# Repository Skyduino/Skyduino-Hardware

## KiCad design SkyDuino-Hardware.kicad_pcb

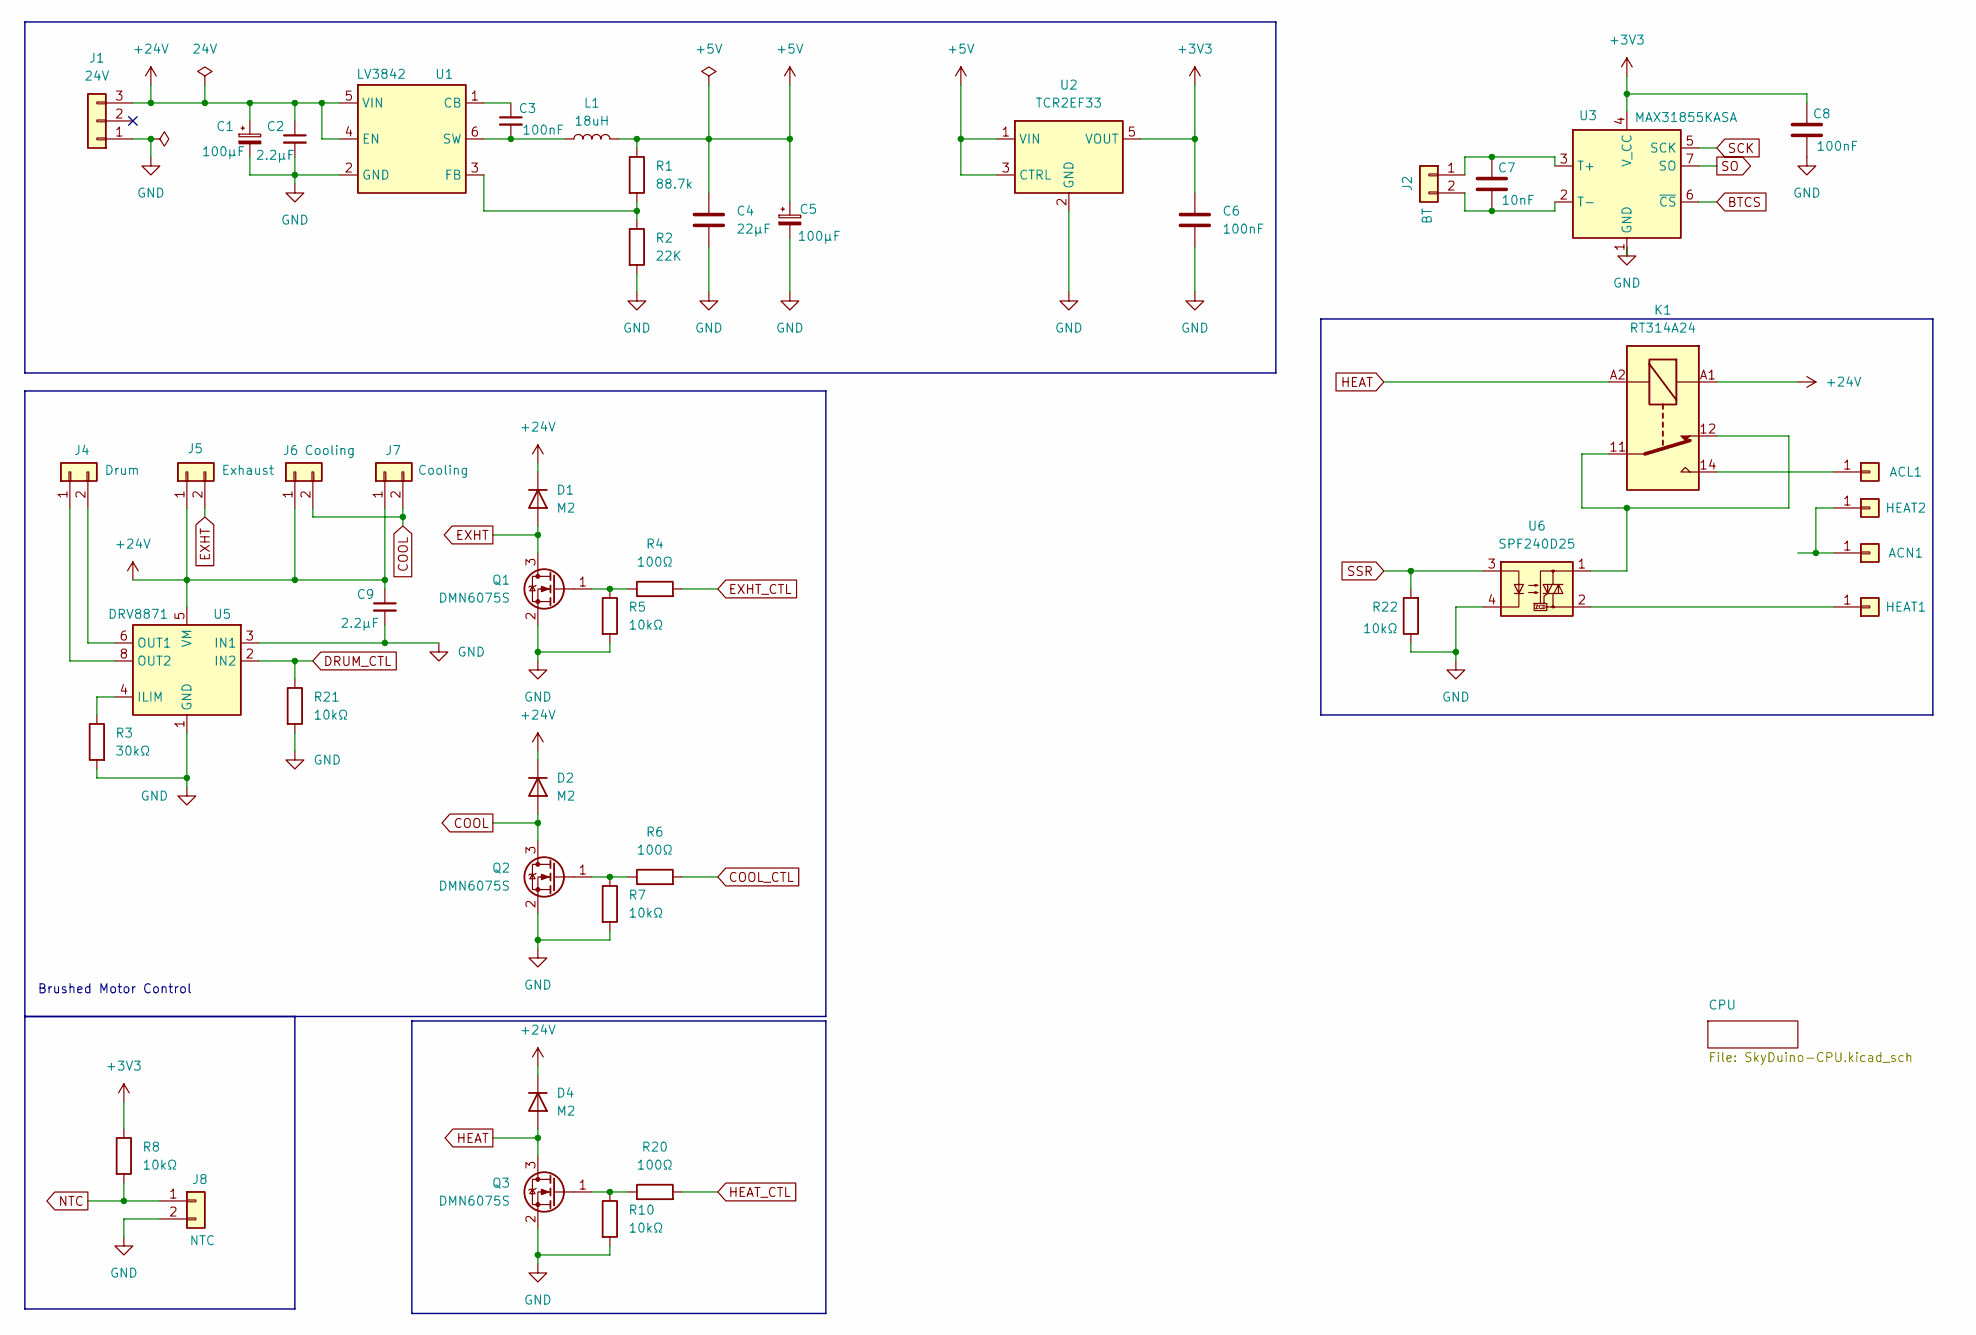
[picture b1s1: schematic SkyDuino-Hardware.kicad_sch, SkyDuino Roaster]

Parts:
ACL1: QC 19705-4303; QuickConnect_Tab_Molex_19705-4303; Mouser p/n 538-19705-4303
ACN1: QC 19705-4303; QuickConnect_Tab_Molex_19705-4303; Mouser p/n 538-19705-4303
C1, C5: 100µF; CP_Radial_D10.0mm_P5.00mm; Mouser p/n 667-ECA-2AM101
C2, C9: 2.2µF; C_0805_2012Metric_Pad1.18x1.45mm_HandSolder; Mouser p/n 187-CL21B225KPFNNNF; LCSC C377773
C3, C6, C8: 100nF; C_0805_2012Metric_Pad1.18x1.45mm_HandSolder; Mouser p/n 810-C2012X7R2A104K; LCSC C49678
C4: 22µF; C_0805_2012Metric_Pad1.18x1.45mm_HandSolder; Mouser p/n 810-C2012X5R1V226MAC; LCSC C45783
C7: 10nF; C_0805_2012Metric_Pad1.18x1.45mm_HandSolder; Mouser p/n 810-C2012C0G1H103J-1; LCSC C1710
D1, D2, D4: M2; D_SMA_Handsoldering; Mouser p/n 637-M2; LCSC C14996
HEAT1, HEAT2: QC 19705-4303; QuickConnect_Tab_Molex_19705-4303; Mouser p/n 538-19705-4303
J1: 24V; JST_XH_B3B-XH-A_1x03_P2.50mm_Vertical
J2: BT; KF7.62_2P
J4: Drum; JST_XH_B2B-XH-A_1x02_P2.50mm_Vertical
J5: Exhaust; JST_XH_B2B-XH-A_1x02_P2.50mm_Vertical
J6, J7: Cooling; JST_XH_B2B-XH-A_1x02_P2.50mm_Vertical
J8: NTC; JST_XH_B2B-XH-A_1x02_P2.50mm_Vertical
K1: RT314A24; Relay_SPDT_Schrack-RT1-16A-FormC_RM5mm; Mouser p/n 655-RT314024
L1: 18uH; L_Bourns_SRN3015BTA; Mouser p/n 652-SRN3015BTA-180M; LCSC C19947604
Q1, Q2, Q3: DMN6075S; SOT-23; Mouser p/n 621-DMN6075S-7; LCSC C155242
R1: 88.7k; R_0805_2012Metric_Pad1.20x1.40mm_HandSolder; Mouser p/n 667-ERA-6AEB8872V; LCSC C706252
R2: 22K; R_0805_2012Metric_Pad1.20x1.40mm_HandSolder; Mouser p/n 603-RT0805DRE0722KL; LCSC C17560
R3: 30kΩ; R_0805_2012Metric_Pad1.20x1.40mm_HandSolder; Mouser p/n 603-RC0805FR-0730KL; LCSC C17633
R4, R6, R20: 100Ω; R_0805_2012Metric_Pad1.20x1.40mm_HandSolder; Mouser p/n 603-AC0805FR-10100RL; LCSC C17408
R5, R7, R8, R10, R21, R22: 10kΩ; R_0805_2012Metric_Pad1.20x1.40mm_HandSolder; Mouser p/n 603-AC0805JR-0710KL; LCSC C17414
U1: LV3842; SOT-23-6; Mouser p/n 595-LV3842XFDBVR; LCSC C5219371
U2: TCR2EF33; SC-74A-5_1.55x2.9mm_P0.95mm; Mouser p/n 757-TCR2EF33LMCT; LCSC C843273
U3: MAX31855KASA; SOIC-8_3.9x4.9mm_P1.27mm; Mouser p/n 700-MAX31855KASA+T; LCSC C52028
U5: DRV8871; Texas_HTSOP-8-1EP_3.9x4.9mm_P1.27mm_EP2.95x4.9mm_Mask2.4x3.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; Mouser p/n 595-DRV8871DDA; LCSC C75864
U6: SPF240D25; SSR_Crydom_SPF240D25; Mouser p/n 558-SPF240D25

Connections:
+3V3: C6.1, C8.1, R8.1, U2.5 (VOUT), U3.4 (V_CC); also elsewhere on the board
+5V: C4.1, C5.1, L1.2, R1.1, U2.1 (VIN), U2.3 (CTRL); also elsewhere on the board
+24V: C1.1, C2.1, C9.1, D1.1 (K), D2.1 (K), D4.1 (K), J1.3, J5.1, J6.1, J7.1, K1.A1, U1.4 (EN), U1.5 (VIN), U5.5 (VM)
BTCS: U3.6 (~CS); also elsewhere on the board
COOL: D2.2 (A), J6.2, J7.2, Q2.3 (D)
COOL_CTL: R6.2; also elsewhere on the board
DRUM_CTL: R21.1, U5.2 (IN2); also elsewhere on the board
EXHT: D1.2 (A), J5.2, Q1.3 (D)
EXHT_CTL: R4.2; also elsewhere on the board
GND: C1.2, C2.2, C4.2, C5.2, C6.2, C8.2, C9.2, J1.1, J8.2, Q1.2 (S), Q2.2 (S), Q3.2 (S), R2.2, R3.2, R5.2, R7.2, R10.2, R21.2, R22.1, U1.2 (GND), U2.2 (GND), U3.1 (GND), U5.1 (GND), U5.3 (IN1), U5.7 (GND), U5.9 (GND), U6.4; also elsewhere on the board
HEAT: D4.2 (A), K1.A2, Q3.3 (D)
HEAT_CTL: R20.2; also elsewhere on the board
NTC: J8.1, R8.2; also elsewhere on the board
unnamed: ACL1.1, K1.14
unnamed: ACN1.1, HEAT2.1
unnamed: HEAT1.1, U6.2
unnamed: C7.1, J2.1, U3.3 (T+)
unnamed: C7.2, J2.2, U3.2 (T-)
unnamed: J4.1, U5.8 (OUT2)
unnamed: J4.2, U5.6 (OUT1)
unnamed: K1.11, K1.12, U6.1
unnamed: Q1.1 (G), R4.1, R5.1
unnamed: Q2.1 (G), R6.1, R7.1
unnamed: Q3.1 (G), R10.1, R20.1
unnamed: C3.1, U1.1 (CB)
unnamed: R1.2, R2.1, U1.3 (FB)
unnamed: C3.2, L1.1, U1.6 (SW)
unnamed: R3.1, U5.4 (ILIM)
SCK: U3.5 (SCK); also elsewhere on the board
SO: U3.7 (SO); also elsewhere on the board
SSR: R22.2, U6.3; also elsewhere on the board

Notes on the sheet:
Brushed Motor Control

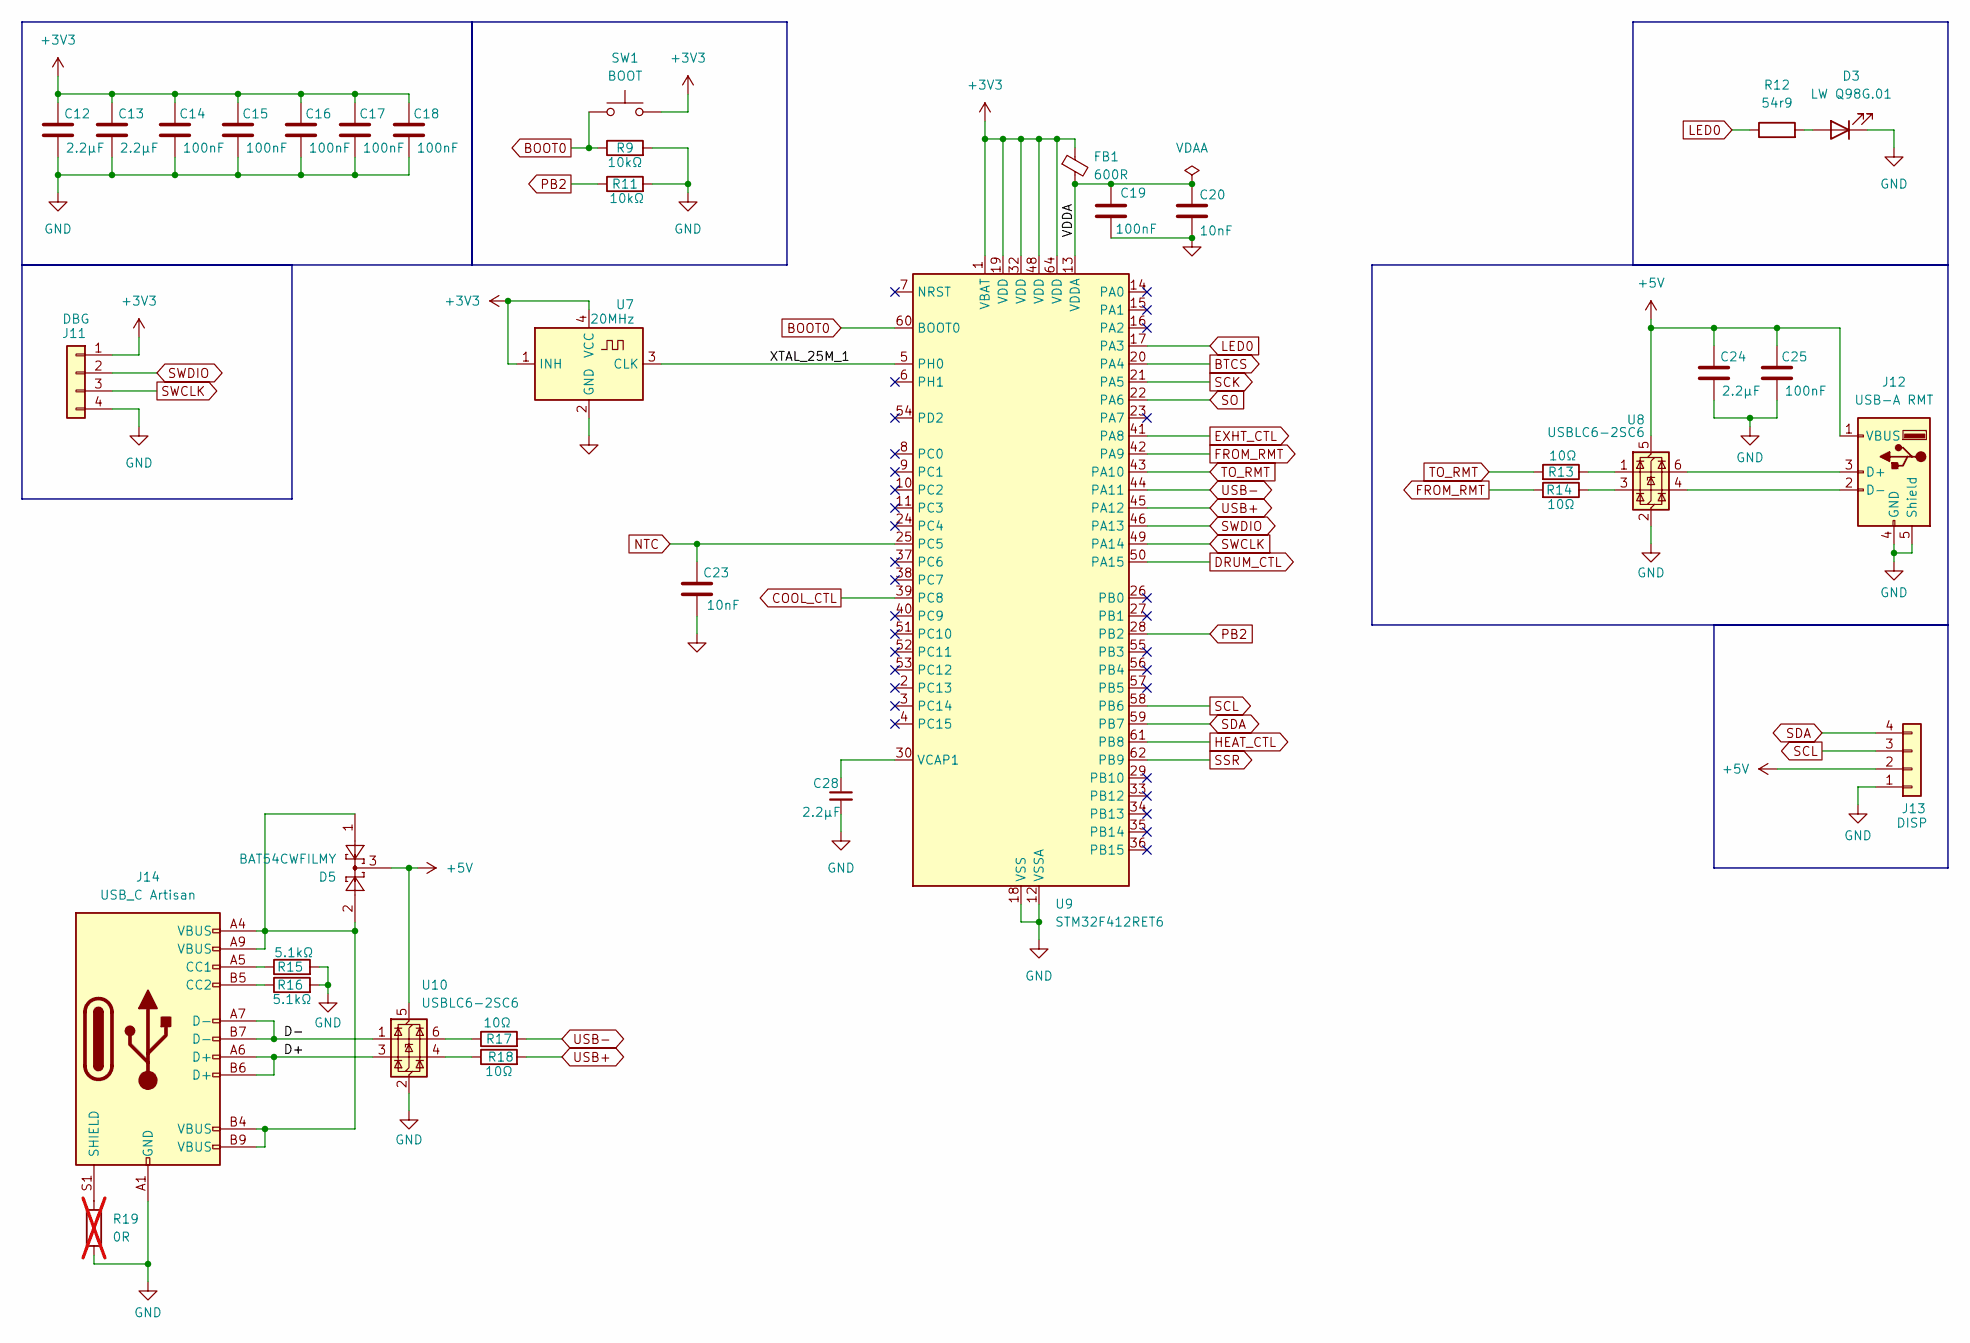
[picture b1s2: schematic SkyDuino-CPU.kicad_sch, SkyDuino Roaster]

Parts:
C12, C13, C24, C28: 2.2µF; C_0805_2012Metric_Pad1.18x1.45mm_HandSolder; Mouser p/n 187-CL21B225KPFNNNF; LCSC C377773
C14, C15, C16, C17, C18, C19, C25: 100nF; C_0805_2012Metric_Pad1.18x1.45mm_HandSolder; Mouser p/n 810-C2012X7R2A104K; LCSC C49678
C20, C23: 10nF; C_0805_2012Metric_Pad1.18x1.45mm_HandSolder; Mouser p/n 810-C2012C0G1H103J-1; LCSC C1710
D3: LW Q98G.01; LED_0805_2012Metric_Pad1.15x1.40mm_HandSolder; Mouser p/n 720-LWQ98G01R2T13K6L; LCSC C34499
D5: BAT54CWFILMY; SOT-323_SC-70; Mouser p/n 511-BAT54CWFILMY; LCSC C2980568
FB1: 600R; L_0805_2012Metric_Pad1.05x1.20mm_HandSolder; Mouser p/n 810-MMZ2012R601AT000; LCSC C1017
J11: DBG; PinHeader_1x04_P2.54mm_Vertical
J12: USB-A RMT; USB_A_Molex_67643_Horizontal_and_AmphenolFCI_87583; Mouser p/n 538-67643-0910
J13: DISP; PinHeader_1x04_P2.54mm_Vertical
J14: USB_C Artisan; USB_C_Receptacle_Molex_Upright; Mouser p/n 538-216989-0001
R9, R11: 10kΩ; R_0805_2012Metric_Pad1.20x1.40mm_HandSolder; Mouser p/n 603-AC0805JR-0710KL; LCSC C17414
R12: 54r9; R_0805_2012Metric_Pad1.20x1.40mm_HandSolder; Mouser p/n 667-ERJ-6ENF54R9V; LCSC C17408
R13, R14, R17, R18: 10Ω; R_0805_2012Metric_Pad1.20x1.40mm_HandSolder; Mouser p/n 603-RC0805FR-1010RL; LCSC C17415
R15, R16: 5.1kΩ; R_0805_2012Metric_Pad1.20x1.40mm_HandSolder; Mouser p/n 603-RC0805JR-135K1L; LCSC C27834
R19: 0R; R_0805_2012Metric_Pad1.20x1.40mm_HandSolder; not fitted
SW1: BOOT; SW_PUSH_6mm_H4.3mm
U7: 20MHz; Oscillator_SMD_Kyocera_KC2520Z-4Pin_2.5x2.0mm; Manufacturer p/n SX2M20.000B10F20TNN; LCSC C7431315
U8, U10: USBLC6-2SC6; SOT-23-6; Mouser p/n 511-USBLC6-2SC6; LCSC C7519
U9: STM32F412RET6; LQFP-64_10x10mm_P0.5mm; Mouser p/n 511-STM32F412RET6; LCSC STM32F412RET6

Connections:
+3V3: C12.1, C13.1, C14.1, C15.1, C16.1, C17.1, C18.1, FB1.1, J11.1, SW1.2, U7.1 (INH), U7.4 (VCC), U9.1 (VBAT), U9.19 (VDD), U9.32 (VDD), U9.48 (VDD), U9.64 (VDD); also elsewhere on the board
+5V: C24.1, C25.1, D5.3, J12.1 (VBUS), J13.2, U8.5 (VBUS), U10.5 (VBUS); also elsewhere on the board
/CPU/D+: J14.A6 (D+), J14.B6 (D+), U10.3 (I/O2)
/CPU/D-: J14.A7 (D-), J14.B7 (D-), U10.1 (I/O1)
/CPU/VDDA: C19.2, C20.2, FB1.2, U9.13 (VDDA)
/CPU/XTAL_25M_1: U7.3 (CLK), U9.5 (PH0)
BOOT0: R9.1, SW1.1, U9.60 (BOOT0)
BTCS: U9.20 (PA4); also elsewhere on the board
COOL_CTL: U9.39 (PC8); also elsewhere on the board
DRUM_CTL: U9.50 (PA15); also elsewhere on the board
EXHT_CTL: U9.41 (PA8); also elsewhere on the board
FROM_RMT: R14.2, U9.42 (PA9)
GND: C12.2, C13.2, C14.2, C15.2, C16.2, C17.2, C18.2, C19.1, C20.1, C23.2, C24.2, C25.2, C28.2, D3.1 (K), J11.4, J12.4 (GND), J12.5 (Shield), J13.1, J14.A1 (GND), J14.A12 (GND), J14.B1 (GND), J14.B12 (GND), R9.2, R11.2, R15.2, R16.2, R19.2, U7.2 (GND), U8.2 (GND), U9.12 (VSSA), U9.18 (VSS), U9.31 (VSS), U9.47 (VSS), U9.63 (VSS), U10.2 (GND); also elsewhere on the board
HEAT_CTL: U9.61 (PB8); also elsewhere on the board
LED0: R12.1, U9.17 (PA3)
NTC: C23.1, U9.25 (PC5); also elsewhere on the board
unnamed: D3.2 (A), R12.2
unnamed: D5.1, D5.2, J14.A4 (VBUS), J14.A9 (VBUS), J14.B4 (VBUS), J14.B9 (VBUS)
unnamed: J12.3 (D+), U8.6 (I/O1)
unnamed: J12.2 (D-), U8.4 (I/O2)
unnamed: J14.A5 (CC1), R15.1
unnamed: J14.B5 (CC2), R16.1
unnamed: J14.S1 (SHIELD), R19.1
unnamed: R13.1, U8.1 (I/O1)
unnamed: R14.1, U8.3 (I/O2)
unnamed: R17.1, U10.6 (I/O1)
unnamed: R18.1, U10.4 (I/O2)
unnamed: C28.1, U9.30 (VCAP1)
PB2: R11.1, U9.28 (PB2)
SCK: U9.21 (PA5); also elsewhere on the board
SCL: J13.3, U9.58 (PB6)
SDA: J13.4, U9.59 (PB7)
SO: U9.22 (PA6); also elsewhere on the board
SSR: U9.62 (PB9); also elsewhere on the board
SWCLK: J11.3, U9.49 (PA14)
SWDIO: J11.2, U9.46 (PA13)
TO_RMT: R13.2, U9.43 (PA10)
USB+: R18.2, U9.45 (PA12)
USB-: R17.2, U9.44 (PA11)

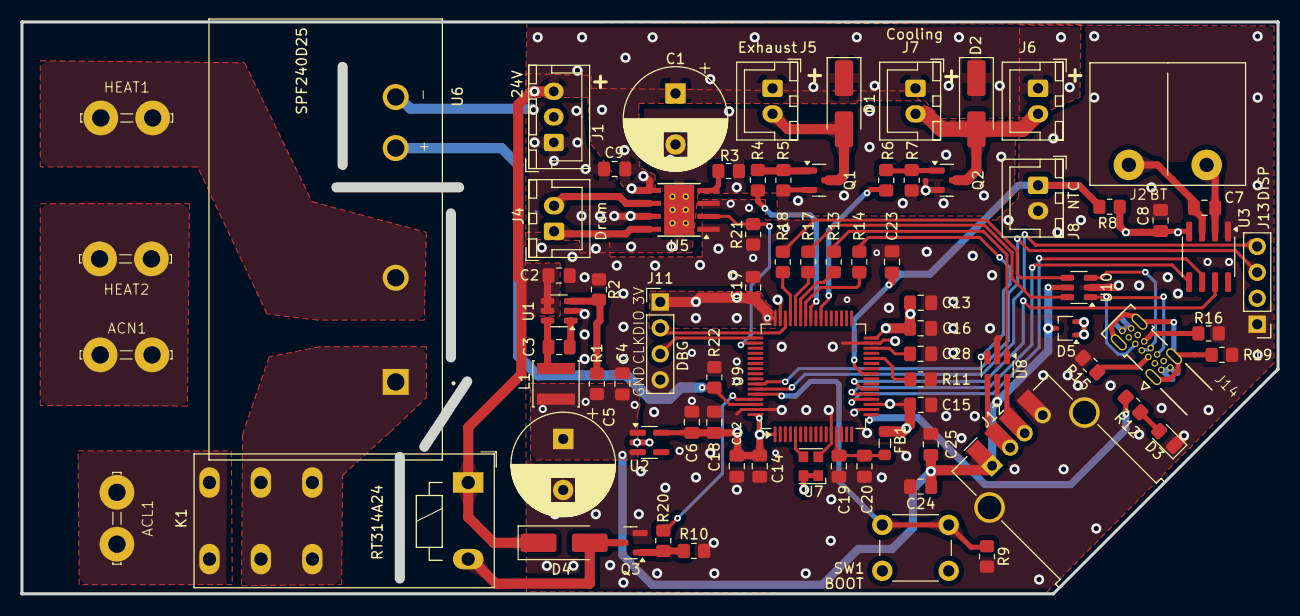
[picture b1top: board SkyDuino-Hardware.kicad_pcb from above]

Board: 4 copper layers, 122.3 x 55.3 mm, 80 parts (0 on the bottom side), 58 nets.

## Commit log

2024-05-04 Add LDO and Motor Controls
    - Add 3v3 LDO
    - Add Motor controls
2024-05-04 Add Max33851 for BT
2024-05-04 Add KF 7.62mm footprint
2024-05-04 Move project footprints libraries into its own folder
2024-05-04 Add Exhaust Temp probe
2024-05-04 Add CPU sheet
2024-05-04 WIP CPU
2024-05-04 WIP CPU boot switches
2024-05-04 Update gitignore
2024-05-04 Add Oscillators
2024-05-04 Rough in on MCU control connections
2024-05-04 Add USB-C connector
2024-05-04 Rename Connector_SH FPs lib
2024-05-04 Update KF7.64 footprint
2024-05-04 Add Footprint for USB-C receptacle
2024-05-05 Update footprint for the boot button
2024-05-06 Add USB-A for the remote
2024-05-07 Add VBat to VDD
2024-05-07 Add two extra 24v connectors
2024-05-07 Add NTC connection
2024-05-07 Add I2C for the display
2024-05-07 Re-annotate. Add NTC capacitor
2024-05-07 Add SSR
2024-05-08 Add Quick Connect Tabs and footprints
2024-05-09 Update footprints
2024-05-09 Use ferrite bead for AVDD
2024-05-09 Optimize pinouts
2024-05-09 Update PCB constraints
2024-05-09 Remove ET TC
2024-05-09 Optimize pinouts, update 2.2uF caps
2024-05-09 PCB WIP
2024-05-10 Mark unconnected STM32 pins
2024-05-11 Add Net Classes
2024-05-11 Add 3d Models
2024-05-11 Rearrange components. Fix 25MHz oscillator connection
2024-05-12 Update USB-C footprint
2024-05-12 WIP PCB tracing
2024-05-12 Remove 25MHz load cap
2024-05-12 Optimize SSR pin
2024-05-12 Optimize LED pin
2024-05-12 PCB Signalling routing
2024-05-12 Copper fill for power
2024-05-12 Label AC lines
2024-05-12 Pour AC lines
2024-05-12 Fix DRC vialations
2024-05-13 Unhide USB-C rec VBUS pins
2024-05-13 Update USB-A 3d model
2024-05-13 update footprint for resistors to hand solder
2024-05-13 Update sheet settings. Add revision text to pcb
2024-05-13 Update 5v pour
2024-05-13 Use same 100nF cap everywhere
2024-05-14 Bump up revision 0.2
2024-05-14 Refactor power rail and optimize pours
2024-05-14 Move SSR GND connection to B layer
2024-05-14 Add silkscreen for DBG/DISP
2024-05-16 Add Heat Safety relay
2024-05-16 WIP DRC
2024-05-17 Use VBus for 3V3 LDO
2024-05-17 Should have saved before commiting
2024-05-22 It is supposed to be STM32F41*2*RET6 MCU
2024-05-29 Move values to User.1 layer
2024-05-29 Refactor VBus/5v feeding
2024-05-30 Update PCB with VBus/5v changes
2024-05-30 Add pull down resistors for SSR and Drum control
2024-05-30 Bump up revision. Use text variables for version control
2024-05-31 Add License
2024-05-31 Fix cutouts, make those 1mm width
2024-05-31 Update symbol fields
2024-05-31 Add kibot file
2024-06-01 Fix KF7.62 FP DRC warnings
2024-06-01 Fix LV3842 ERC warnings
2024-06-01 Fix ERC/DRC warnings
2024-06-01 Update kibot config
2024-06-01 Fix warning for the step down converter
2024-06-01 Ibom extra fields and printing fixes
2024-06-01 Add User.1 layer to PDF fab layers printout
2024-06-01 cleanups
2024-06-01 Exclude project bak files from version control
2024-06-01 Filter DRC edge errors caused by cutouts
2024-06-01 Mostly copper pours optimizations
2024-06-01 Update Kibot PDF output, include inner copper layers
2024-06-01 fixup
2024-06-01 No blender rendering, because of the edge cutouts
2024-06-01 Initial Github Action
2024-06-02 Alow manual action call
2024-06-03 GHA: Duh
2024-06-03 Don't silk variant on PCB
2024-06-03 GHA: fixup
2024-06-03 Always upload artifacts
2024-06-03 GHA: can't spell...
2024-06-03 Rename GHA action
2024-06-03 Fix Drill output
2024-06-03 Make kibot action callable
2024-06-03 Add permissions to release drafter
2024-06-03 Add releaser and assets uploading
2024-06-03 Add checkout step
    Zip files manually
    Use Minor versioning for the Release drafter
2024-06-03 Change rev to dev tag. Don't print variant
2024-06-04 Don't skip all of preflight in separate jobs
2024-06-04 Kickoff asset upload from Kibot action workflow
2024-06-04 I'm really bad at this, but I'll get this working
2024-06-04 Change triggers for release uploads
2024-06-04 Update release drafter template
2024-06-04 Update connector descriptions
2024-06-04 Revision 0.3
2024-06-04 Bump up revision 0.4.dev
2024-06-04 RC 0.3 (#1)
    Initial RC
2024-06-04 Fix GH event name
2024-06-05 Add GIT Tag when available
2024-06-05 Release Candidation version 0.4
2024-06-05 Bump up revision 0.5.dev
2024-06-10 JLCPCB and Revision tagging
    - Generate JLCPCB assembly files: BoM & Position
    - Tag revisions based on Git Tags
2024-06-10 Add Config field and exclude TH components from assembly
2024-06-10 Update LCSC field
2024-06-10 Add JLC rotation offsets
2024-06-11 Rotate U5 in correct direction
2024-06-11 Add Alternative USB-C connector
2024-06-11 Add Footprints and 3D models for the alternative USB-C connectors
2024-06-28 Make it fit the vented coffin enclosure.
2024-06-28 Reposition SSR to fit into vented enclosure
2024-06-28 Move capacitor, 24v conn & TC conn
2024-06-28 Reroute SSR control track
2024-06-28 Fix DRC
2024-07-05 Swap AC-Live and AC-Neutral on PCB
    Swap Live with Neutral on PCB, so the live is controlled by the Relay.
2024-07-05 Swap AC-Live and AC-Neutral on PCB (#9)
    Swap Live with Neutral on PCB, so the live is controlled by the Relay.
2024-08-13 Upload diffs to Releases
2024-08-14 Split diff into a separate workflow and run it unconditionally
2024-08-14 Doh!
2024-08-14 Print last release tag for Kidiff
2024-08-14 Doh #2
2024-08-14 Checkout first
2024-08-14 Print Kidiff "old" value
2024-08-14 Diff directory is stripped on artifact upload
2024-08-14 Refactor how last commit for Kidiff is obtained
2024-08-14 Print "last tag" to be used for Kidiff
2024-08-14 Print "last tag" to be used for Kidiff (#19)
2024-08-14 Use labels for Release Drafter
2024-08-14 Use labels for version resolving
2024-08-15 Use version resolver (#23)
    * Use resolved_version for Release naming/versioning
    * Pring event name if debug is enabled
    * By default all release drafts are pre-releases
    * Use main for commitish
    * Update tag-prefix for release drafter
    * Re-run release drafter if new labels are applied
2024-08-16 Mirror i2c line labels on the back silk layer
2024-08-16 Mirror i2c line labels on the back silk layer (#24)
2024-08-16 Remove debug logging
2024-08-16 Remove debug logging (#25)
2024-08-17 Add a footprint for a combined Molex 67643 and Amphenol FCI 87583 USB A receptacle
2024-08-17 Add alternative part number for USB-A receptacle
    Use Amphenol FCI 87583 USB-A receptacle as an alternative part and
    update footprint to use the combined footprint of both connectors
2024-08-17 Use a combined Molex/Amphenol USB-A footprint
2024-08-17 Merge pull request #26
    Alternative USB-A receptacle connector
2024-08-17 Use dev as the commitish for release drafter
2024-08-17 Use dev as the commitish for release drafter (#27)
2024-08-17 Move Revision/Board silk printing so it is not clipped by the cutouts
2024-08-17 Move Revision/Board silk printing so it is not clipped by the cutouts (#28)
